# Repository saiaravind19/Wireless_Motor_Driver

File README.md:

## Wireless Motor Driver ##

Motor Drivers are popular among Robotics/ Hardware Enthusiasts to build various cool projects. One of the most popular among them is the L298N motor driver. Conventionally, we use the motor driver, a bunch of wires and connect it to our microcontroller to control different actuators. But in our version of the Motor Driver, we have  made it into a one stop solution by removing the excess of wires and connecing the Wemos DI mini microcontroller, all in one single PCB!

Wemos D1 mini was chosen for it WiFi functionality. We have our own GUI through which the motor driver can be controlled. One of the main objective of making this Motor Driver was to reduce the time to prototype projects and also to make your bots completely wireless. You can simply connect the motors and control it via your mobile through WiFi. That's how simple it is!

## Specifications
- Supply Voltage: 6 - 12V
- Output Current: 1.2A (max)
- 500mA Fuse Protection for Wemos D1 mini
- Can be used separately as a conventional L298N Motor Driver as well

## Prerequisites 
- Make sure you install one of the [supported version](https://www.arduino.cc/en/software/OldSoftwareReleases) of Arduino IDE and have ESP8266 core installed.
     - Package is tested with Arduino IDE v 1.8.5  <-> plugin v 0.5.0 so it is recommended to use the same.
- To install [Spiffs files uploader](https://github.com/me-no-dev/arduino-esp32fs-plugin) please follow installation tutorials provided in the tutorial.
- Once the plugging and Arduino IDE are installed successfully move on to next step of  installation of stack to controller.

## Installation
- Clone the repo to the system  and open the project in Arduino IDE.
  -  _**Note:Make sure data folder is present in current working directory.**_
- Use spiffs files uploader to flash the HTML UI to ESP. To upload navigate to Tools>ESP8266 Sketch Data Upload.
- Wait for the files to upload once the files are uploaded, compile and upload the program.
     - _**Note:Once the files are uploaded no need to reupload file each time a new code is flashed.**_ 

## Pinout Connections

| Controller Gpio  | MotorDriver pin|
| ------ | ------ |
|    D1    | EN1       |
|    D5    | IN1       |
|    D6   | IN2       |
|    D2    | EN2       |
|    D7    | IN3       |
|    D8   | IN4       |
|    D3    | L1-led       |
|    D0    | L2-led       |

## Accessing UI
- In case using ESP as Access point(AP mode) connect to the network SSID mentioned in the file **data>wifi>ap.txt** present in the working directory.
- Open your favourite web browser and type **wirelessmd.local** and the UI pops up in the browser and you are ready to control the motors wirelessely.

## Hardare
  All of the schematic and board layout files are present in this folder. The PCB was designed using KiCAD 6.0 version.
The board is based upon the popular Dual Full Bridge Motor Driver L298N and the miniature wireless microntroller development board Wemos D1 mini. The PCB can output nearly 1.2A per channel. Since it has the Wemos D1 mini on board, it gives the user the capability to control the motors wwirelessly using our unique GUI.

- WirelessMD/Hardware/KiCAD Project - Contains the KiCAD Project File 
- WirelessMD/Hardware/WirelessMD_sch.pdf - Schematic of Wireless Motor Driver PCB

## Demo Video

https://github.com/saiaravind19/WirelessMD/assets/73806646/1ec77462-335a-4383-b794-b8709d903f12

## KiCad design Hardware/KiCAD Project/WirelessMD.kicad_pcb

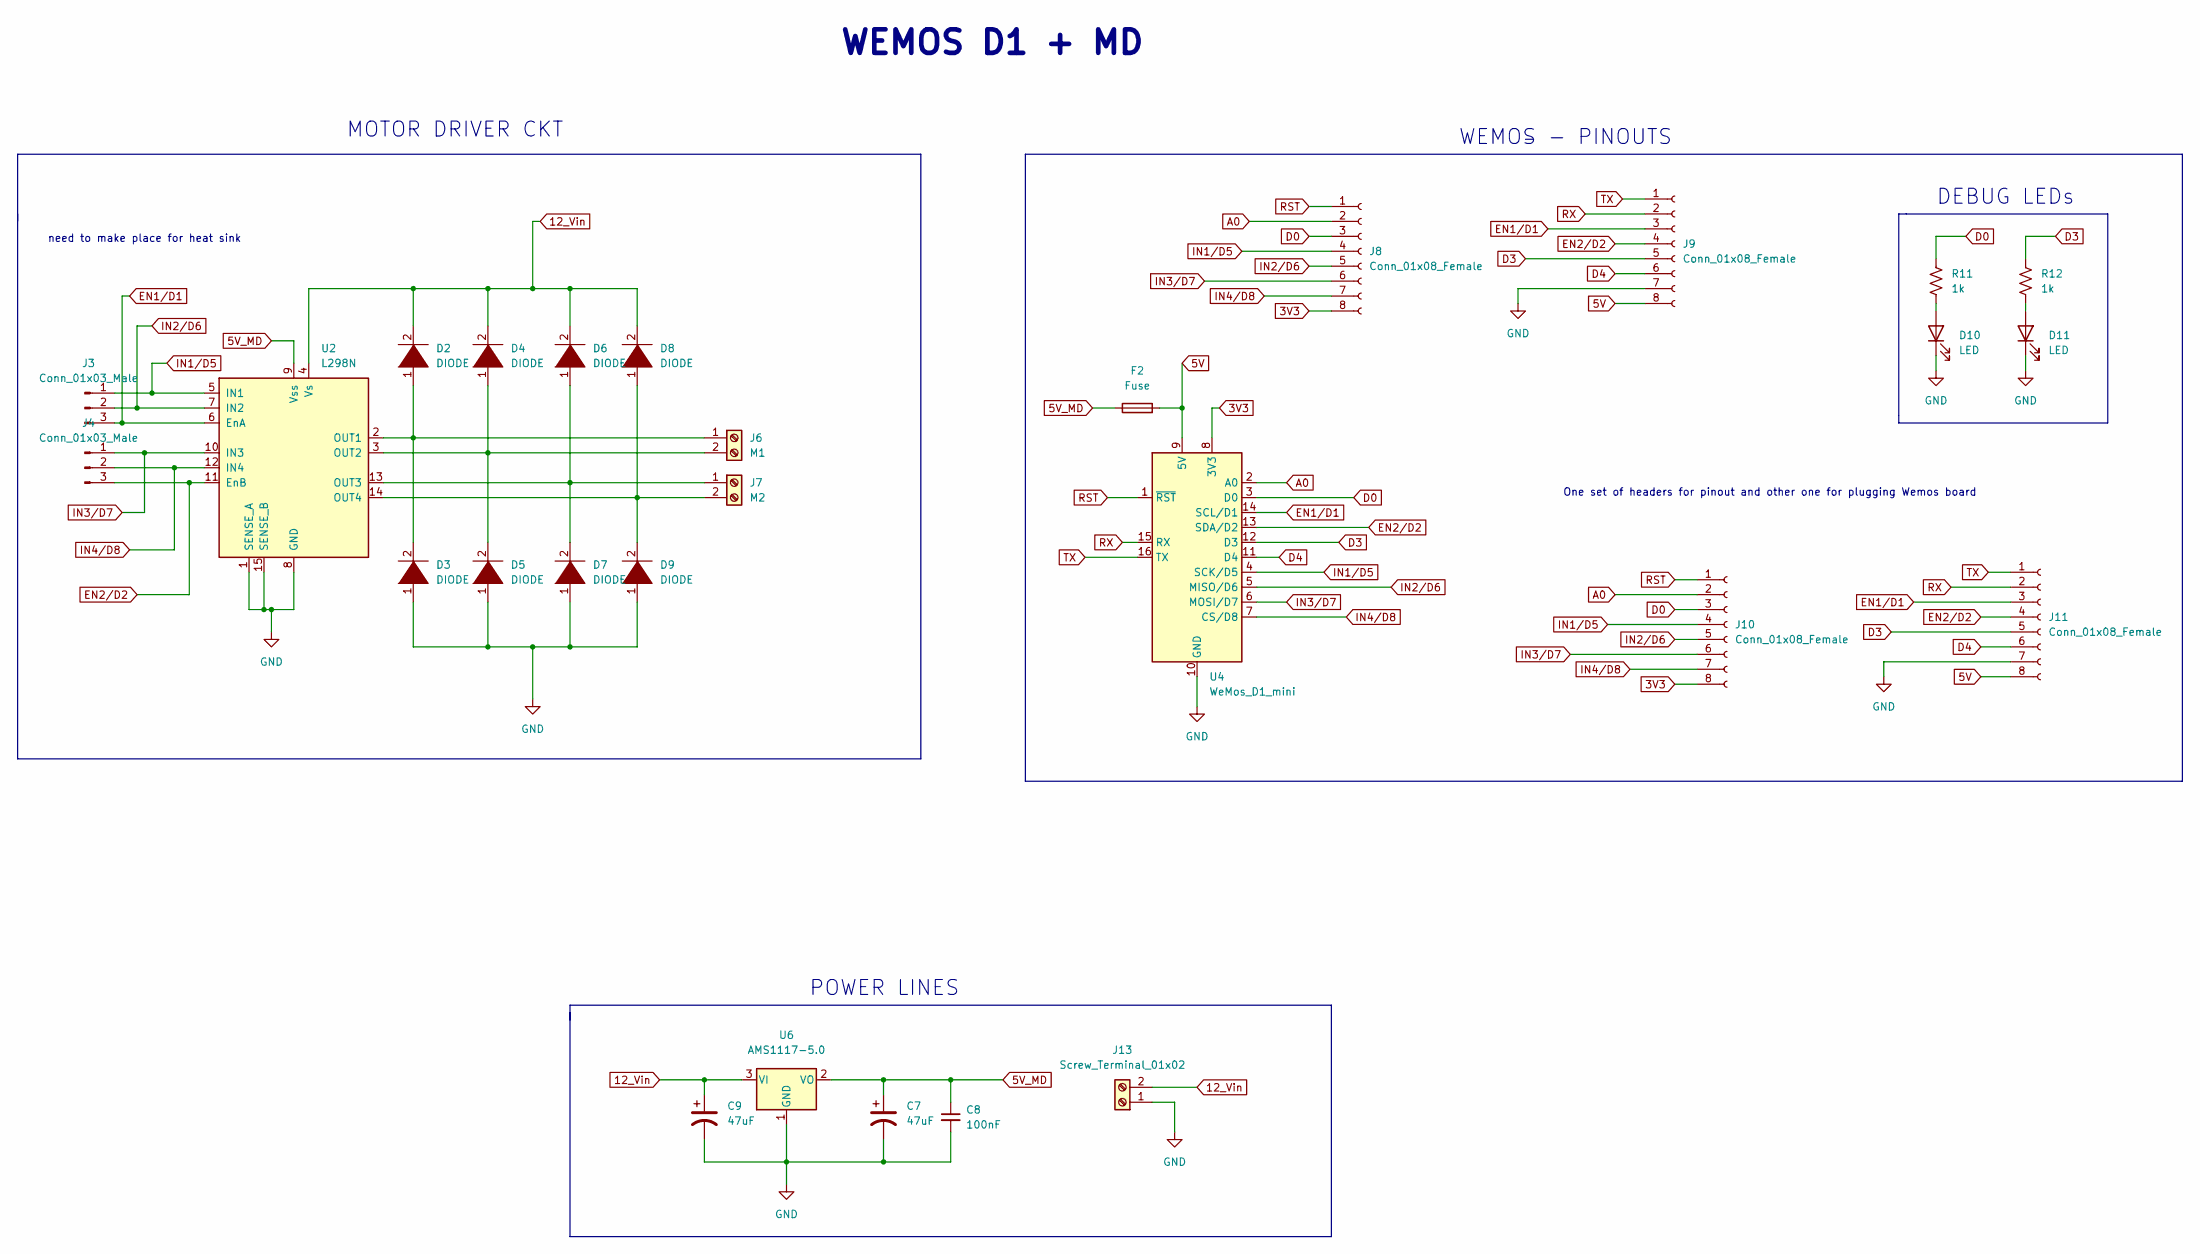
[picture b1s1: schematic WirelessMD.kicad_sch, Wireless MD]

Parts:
C7, C9: 47uF; 1206
C8: 100nF; 0805
D2, D3, D4, D5, D6, D7, D8, D9: DIODE; D_SMA_Handsoldering
D10, D11: LED; 0805
F2: Fuse; 1206
J3, J4: Conn_01x03_Male; PinHeader_1x03_P2.54mm_Vertical
J6: M1; TerminalBlock_bornier-2_P5.08mm
J7: M2; TerminalBlock_bornier-2_P5.08mm
J8, J9, J10, J11: Conn_01x08_Female; PinHeader_1x08_P2.54mm_Vertical
J13: Screw_Terminal_01x02; TerminalBlock_bornier-2_P5.08mm
R11, R12: 1k; 0805
U2: L298N; TO-220-15_P2.54x2.54mm_StaggerOdd_Lead4.58mm_Vertical
U4: WeMos_D1_mini; WEMOS_D1_mini_light
U6: AMS1117-5.0; SOT-223

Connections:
3V3: J8.8, J10.8, U4.8 (3V3)
5V: F2.2, J9.8, J11.8, U4.9 (5V)
5V_MD: C7.1, C8.1, F2.1, U2.9 (Vss), U6.2 (VO)
12_Vin: C9.1, D2.2 (A), D4.2 (A), D6.2 (A), D8.2 (A), J13.2, U2.4 (Vs), U6.3 (VI)
A0: J8.2, J10.2, U4.2 (A0)
D0: J8.3, J10.3, R11.2, U4.3 (D0)
D3: J9.5, J11.5, R12.2, U4.12 (D3)
D4: J9.6, J11.6, U4.11 (D4)
EN1/D1: J3.3, J9.3, J11.3, U2.6 (EnA), U4.14 (SCL/D1)
EN2/D2: J4.3, J9.4, J11.4, U2.11 (EnB), U4.13 (SDA/D2)
GND: C7.2, C8.2, C9.2, D3.1 (K), D5.1 (K), D7.1 (K), D9.1 (K), D10.1 (K), D11.1 (K), J9.7, J11.7, J13.1, U2.1 (SENSE_A), U2.8 (GND), U2.15 (SENSE_B), U4.10 (GND), U6.1 (GND)
IN1/D5: J3.1, J8.4, J10.4, U2.5 (IN1), U4.4 (SCK/D5)
IN2/D6: J3.2, J8.5, J10.5, U2.7 (IN2), U4.5 (MISO/D6)
IN3/D7: J4.1, J8.6, J10.6, U2.10 (IN3), U4.6 (MOSI/D7)
IN4/D8: J4.2, J8.7, J10.7, U2.12 (IN4), U4.7 (CS/D8)
unnamed: D2.1 (K), D3.2 (A), J6.1, U2.2 (OUT1)
unnamed: D4.1 (K), D5.2 (A), J6.2, U2.3 (OUT2)
unnamed: D6.1 (K), D7.2 (A), J7.1, U2.13 (OUT3)
unnamed: D8.1 (K), D9.2 (A), J7.2, U2.14 (OUT4)
unnamed: D10.2 (A), R11.1
unnamed: D11.2 (A), R12.1
RST: J8.1, J10.1, U4.1 (~RST)
RX: J9.2, J11.2, U4.15 (RX)
TX: J9.1, J11.1, U4.16 (TX)

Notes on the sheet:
POWER LINES
DEBUG LEDs
WEMOS - PINOUTS
need to make place for heat sink
MOTOR DRIVER CKT
WEMOS D1 + MD
One set of headers for pinout and other one for plugging Wemos board

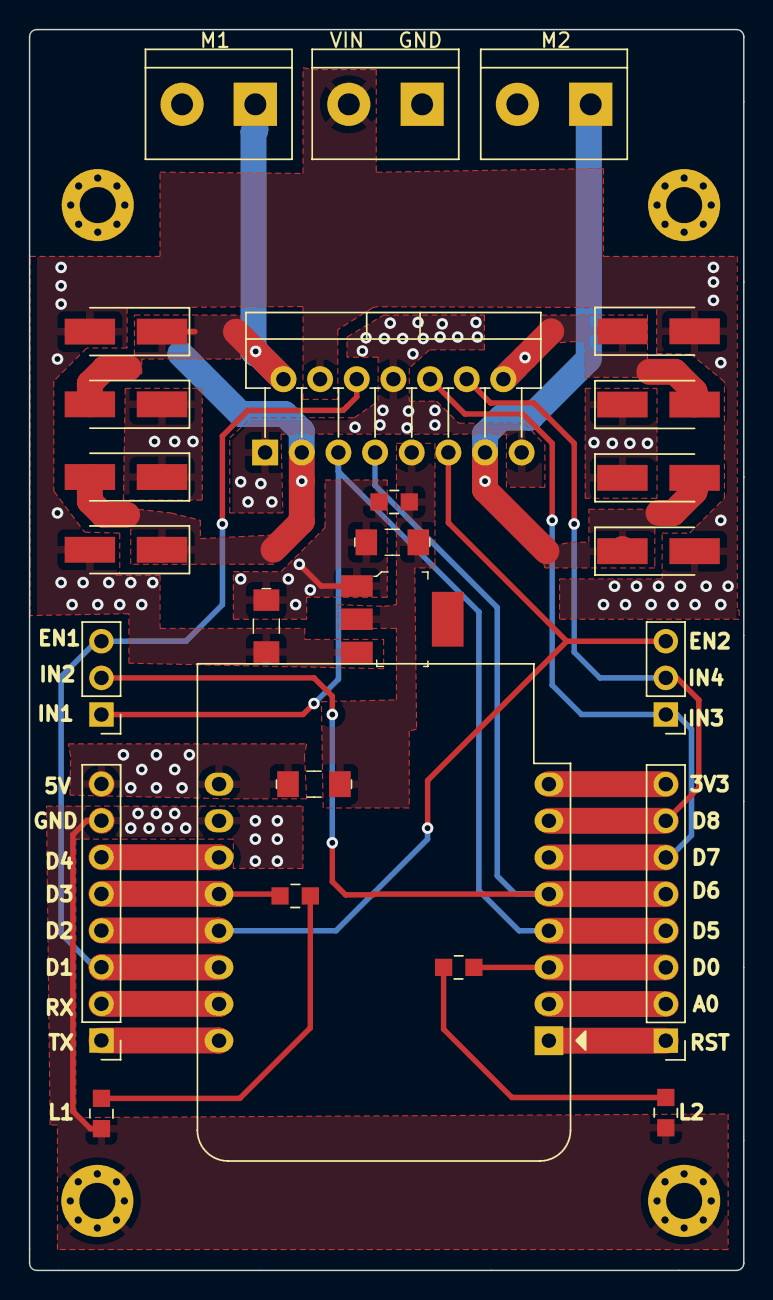
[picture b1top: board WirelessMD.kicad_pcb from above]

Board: 2 copper layers, 49.5 x 86.0 mm, 26 parts (0 on the bottom side), 24 nets.

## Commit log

2023-02-05 implemented start button in the hoem page
2023-02-05 added header file and ideation for STA mode form
2023-02-08 v0.1 with ESP as STA mode
2023-02-08 fix for wifi module reset on AP mode
2023-02-13 Fix for sap mode
2023-02-14 form is integrated with spniffs file system.
2023-02-18 added home button to joystick page
2023-02-18 removed unwanted comments
2023-02-21 Mdns integrated need to work on structuring code
2023-02-26 added mode page
2023-02-26 added home button in mode page
2023-03-05 dissabled view in sap mode implemented ap mode connect and sap mode connect
2023-04-13 updated installation tutorials
2023-04-13 Update README.md
    added arduino older version link
2023-04-13 Update README.md
    Added pinout
2023-05-19 Create test
2023-05-21 added rccar image
2023-05-21 added motor driver picture
2023-05-21 Update README.md
    added motor driver image
2023-05-21 Update README.md
    updated width size
2023-06-14 uploaded demo video
2023-06-17 Add files via upload
    replacing robot image
2023-06-17 updated images
